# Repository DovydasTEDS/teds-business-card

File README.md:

# teds business card

an nfc business card with (i think) cool (sorta) artwork which took me longer than it should've  
it also has a qr code  

Bill of materials (2x PCBA JLCPCB):  
- PCBA from JLCPCB: $23.78 ($17.07 + $6.76 shipping)
  
|Item|LCSC Part                    |Price per Unit|No.                                          |Total Price|Description                                  |
|----|-----------------------------|--------------|---------------------------------------------|-----------|---------------------------------------------|
|    |C21120                       |$0.02         |1                                            |$0.02      |Ceramic Capacitor                            |
|    |C34499                       |$0.04         |1                                            |$0.04      |White LED                                    |
|    |C23182                       |$0.00         |1                                            |$0.00      |47 Ohm Resistor                              |
|    |C710403                      |$1.44         |1                                            |$1.44      |NFC Chip                                     |
|PCB |                             |$1.00         |5                                            |$5.00      |PCB (5x for $2)                              |
|Shipping|                             |$6.71         |1                                            |$6.71      |Global Direct Standard Line JLCPCB           |
|    |Total                        |              |                                             |$13.21     |Total will not be accurate due to PCBA costs=|

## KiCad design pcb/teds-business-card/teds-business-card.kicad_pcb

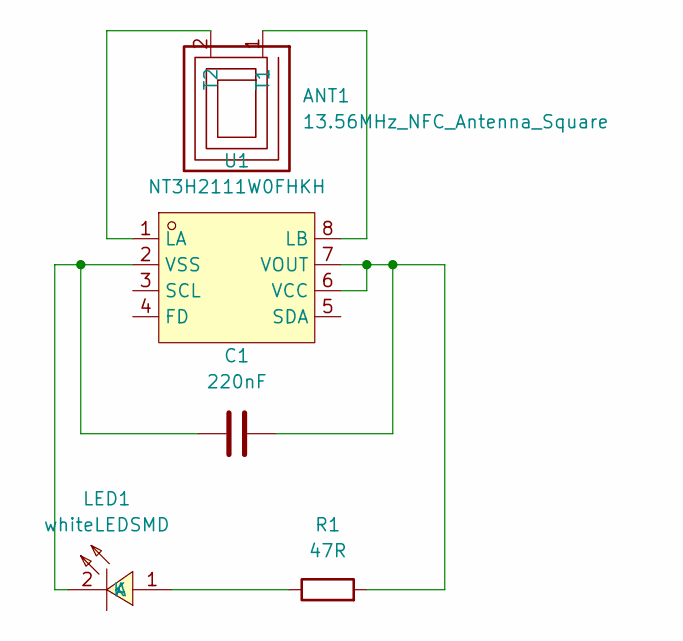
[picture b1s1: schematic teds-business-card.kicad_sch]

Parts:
ANT1: 13.56MHz_NFC_Antenna_Square; NFC_60x49_N3_NXP_NTAG_I2C_Plus_NT3H2111
C1: 220nF; C0603
LED1: whiteLEDSMD; LED0805-R-RD; MPN KT-0805W; LCSC Part C34499
R1: 47R; R_0603_1608Metric
U1: NT3H2111W0FHKH; XQFN-8_L1.6-W1.6-P0.50-BL_NT3H2111W0FHKH; MPN NT3H2111W0FHKH; LCSC Part C710403

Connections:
unnamed: ANT1.1 (T1), U1.8 (LB)
unnamed: ANT1.2 (T2), U1.1 (LA)
unnamed: LED1.1 (A), R1.1
unnamed: C1.1, LED1.2 (K), U1.2 (VSS)
unnamed: C1.2, R1.2, U1.6 (VCC), U1.7 (VOUT)

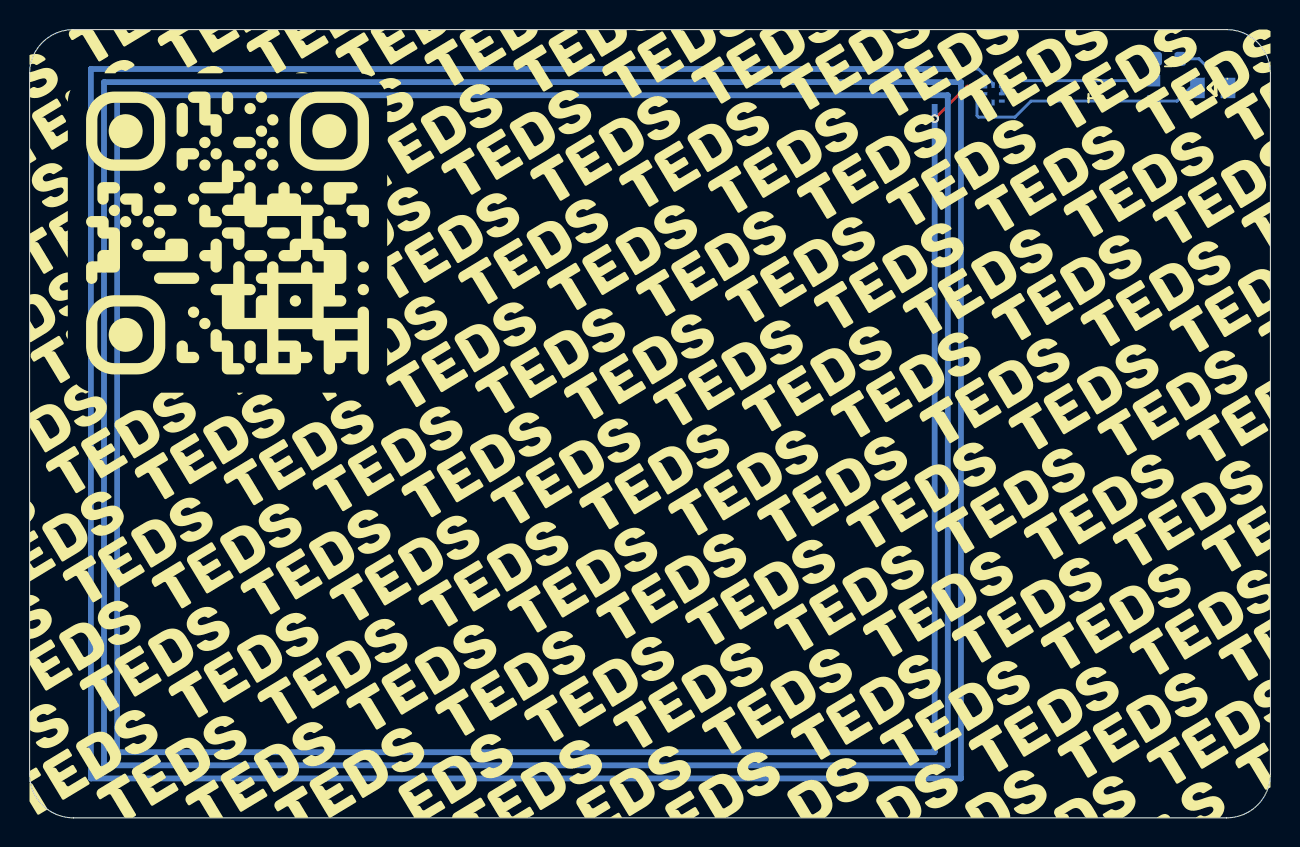
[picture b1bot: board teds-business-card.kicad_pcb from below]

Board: 2 copper layers, 85.0 x 54.0 mm, 5 parts (5 on the bottom side), 5 nets.

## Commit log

2026-05-25 add gitignore
2026-05-25 add readme
2026-05-25 add prod files
2026-06-18 add bom
2026-06-18 add bom csv
2026-06-25 add jlc bom + jlc screenshot... THANK YOU GITIGNORE :)
